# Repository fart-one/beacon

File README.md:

### Toilet transmitter
## Prerequisites

# Tools
*  [Arduino ESP8266 filesystem uploader](https://github.com/esp8266/arduino-esp8266fs-plugin)

# Libraries
*  [ArduinoJson](https://github.com/bblanchon/ArduinoJson)
*  [Configuration](https://github.com/fart-one/configuration)

# Startup procedure
* Install Tools
* Add dependencies
* Rename `config.json.example` to `config.json`
* Edit `config.json` with your own configuration
* Upload configuration `Tools` -> `ESP8266 Sketch Data Upload`
* Compile and upload sketch

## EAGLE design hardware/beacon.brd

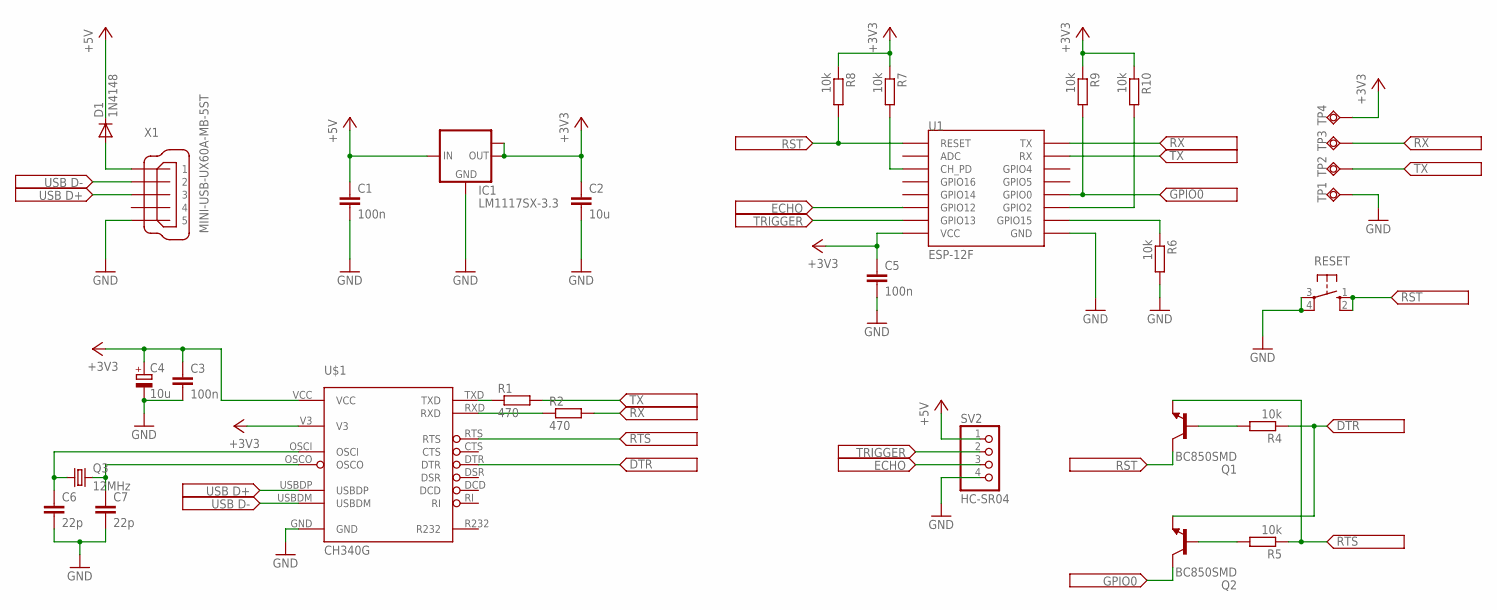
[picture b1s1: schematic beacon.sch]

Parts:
C1, C3, C5: 100n; C1206K
C2: 10u; C1206K
C4: 10u; 175TMP-0810
C6, C7: 22p; C1206K
D1: 1N4148; SMA
IC1: LM1117SX-3.3; TO263
Q1, Q2: BC850SMD; SOT23-BEC
Q3: 12MHz; SM49
R1, R2: 470; R1206
R4, R5, R6, R7, R8, R9, R10: 10k; R1206
RESET: 10-XX; B3F-10XX
SV2: HC-SR04; 1X04/90
TP1, TP2, TP3, TP4: TPSQTP20SQ; TP20SQ
U1: ESP-12F; ESP12-SMD
U$1: CH340G; SOP16
X1: MINI-USB-UX60A-MB-5ST; UX60A-MB-5ST

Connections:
+3V3: C2.1, C3.1, C4.+, C5.1, IC1.2 (OUT), IC1.TAB (OUT1), R7.1, R8.1, R9.1, R10.1, TP4.TP, U1.VCC, U$1.V3, U$1.VCC
+5V: C1.1, D1.C, IC1.3 (IN), SV2.1
DTR: Q2.E, R4.1, U$1.DTR
ECHO: SV2.3, U1.GPIO12
GND: C1.2, C2.2, C3.2, C4.-, C5.2, C6.2, C7.2, IC1.1 (GND), R6.2, RESET.3, RESET.4 (P1), SV2.4, TP1.TP, U1.GND, U$1.GND, X1.5
GPIO0: Q2.C, R9.2, U1.GPIO0
unnamed: R1.1, U$1.TXD
unnamed: R2.1, U$1.RXD
unnamed: C6.1, Q3.1, U$1.OSCI
unnamed: C7.1, Q3.2, U$1.OSCO
unnamed: D1.A, X1.1
unnamed: R6.1, U1.GPIO15
unnamed: R7.2, U1.CH_PD
unnamed: Q1.B, R4.2
unnamed: Q2.B, R5.2
unnamed: R10.2, U1.GPIO2
RST: Q1.C, R8.2, RESET.1 (S), RESET.2 (S1), U1.RESET
RTS: Q1.E, R5.1, U$1.RTS
RX: R2.2, TP3.TP, U1.TXD0 (TX)
TRIGGER: SV2.2, U1.GPIO13
TX: R1.2, TP2.TP, U1.RXD0 (RX)
USBDM: U$1.USBDM, X1.2
USBDP: U$1.USBDP, X1.3

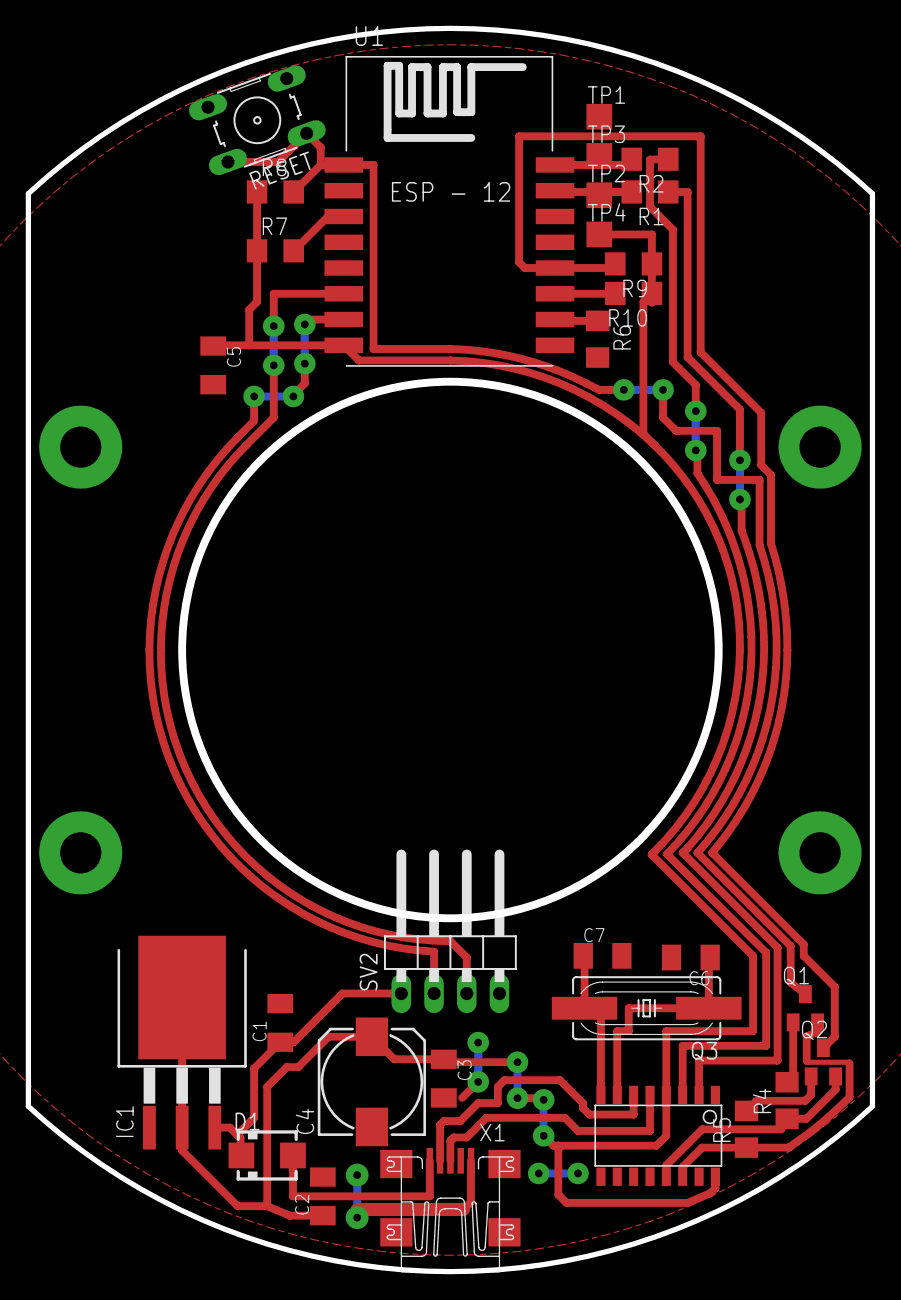
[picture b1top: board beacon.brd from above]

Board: 2 copper layers, 65.3 x 96.3 mm, 30 parts (0 on the bottom side), 23 nets.

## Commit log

2017-04-06 trully first working copy ....
2017-04-06 +deepSleep
2017-04-06 -deepSleep + comments
2017-04-07 wifi + mqtt tests
2017-04-07 send all measurements to mqtt
2017-04-08 refactoring
2017-04-08 message as JSON + refactoring
2017-04-08 add multiple samples per measure, calculating average
2017-04-08 fix missing files
2017-04-09 add hysteresis, add unknown status
2017-04-10 +using external config on SPIFFS - readConfig() +proper json buffer types
2017-04-10 clenup
2017-04-20 add eagle file, update gitignore for eagle, add hardware datasheed, add external libraries
2017-04-26 sleep(10), UNOCCUPIED_DISTANCE=80
2017-04-26 corrected memory leak
2017-04-28 add delay when occupied
2017-04-29 update schematic
2017-05-01 update schematic, change ft232 to ch340g
2017-05-02 create board, update ch340g lbr
2017-05-03 add brd
2017-05-04 +TLS (fingerprint checking)
2017-05-07 add test pads
2017-06-04 init
2017-06-13 add config.json, update readme, create sketch files
